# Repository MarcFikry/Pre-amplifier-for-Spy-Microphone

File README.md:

# Pre-amplifier for Spy Microphone 

## Project Overview
This project was carried out as part of the **1A Bureau d'Étude d'Électronique (Electronics Design Project)** at **Grenoble INP – Phelma**, during the first semester of the **Physics, Electronics and Telecommunications (PET)** engineering program.

The objective was to design and implement a **pre-amplifier for an electret microphone**, which could be later connected to an FM transmitter.  
Which includes the following functional blocks:
- Microphone biasing and pre-amplification
- Adjustable volume control
- Sound detection via a LED indicator

All circuits were powered under **asymmetrical supply (0–5 V)** and implemented using **MCP6002 operational amplifiers**.

---

## Features
- **Electret Microphone Biasing** — converts the small current variations from the microphone into voltage.  
- **Variable Gain Amplifier** — amplifies weak audio signals with adjustable sensitivity.  
- **Volume Control** — allows amplitude adjustment before the output stage to avoid distortion.  
- **Sound Detection LED** — implemented with a comparator with hysteresis to indicate when a sound is detected.  
- **Power Supply:** 0 – 5 V (single supply)  

---

## Design and Implementation
- Circuit **designed and simulated in KiCad**
- **Component sizing** based on theoretical transfer functions and Bode plots  
- **PCB routing** performed in KiCad, ensuring clean signal paths and proper grounding  
- **PCB manufacturing** followed by **manual soldering** and **experimental validation**  
- Tested using **oscilloscope** and **function generator** to verify:
  - Correct biasing
  - Amplification gain and frequency response
  - Proper LED threshold behavior

---

## Project Images

### Schematic Diagram  

### PCB Layout (Design in KiCad)  

### Printed PCB (Before Soldering)  

### Assembled Board (After Soldering)  

---

## Components Used
| Component | Description | Note |
|------------|--------------|------|
| MCP6002 | Dual Operational Amplifier | 0–5 V single-supply compatible |
| Electret Microphone | Audio input sensor | Requires biasing resistor |
| Resistors / Potentiometers | Gain and volume adjustment | E12 standard series |
| LED + Comparator | Sound level indicator | Implemented with hysteresis |
| Capacitors | AC coupling and filtering | 50 Hz–20 kHz bandpass design |

---

## Results
- Clean and stable amplification of the audio signal  
- Adjustable output amplitude via volume potentiometer  
- Reliable LED indication of detected sound  
- Measured gain and frequency response consistent with theoretical predictions  

---

## Tools and Environment
- **Software:** KiCad, Oscilloscope interface tools  
- **Hardware:** Breadboard, 0–5 V power supply, Function generator   

---

## Acknowledgments
Project supervised by:
- **Nicolas Ruty**
- **Fanny Poinsotte**
- **Matthieu Guerquin-Kern**

Grenoble INP – Phelma, 1A PET (Tronc Commun)

---

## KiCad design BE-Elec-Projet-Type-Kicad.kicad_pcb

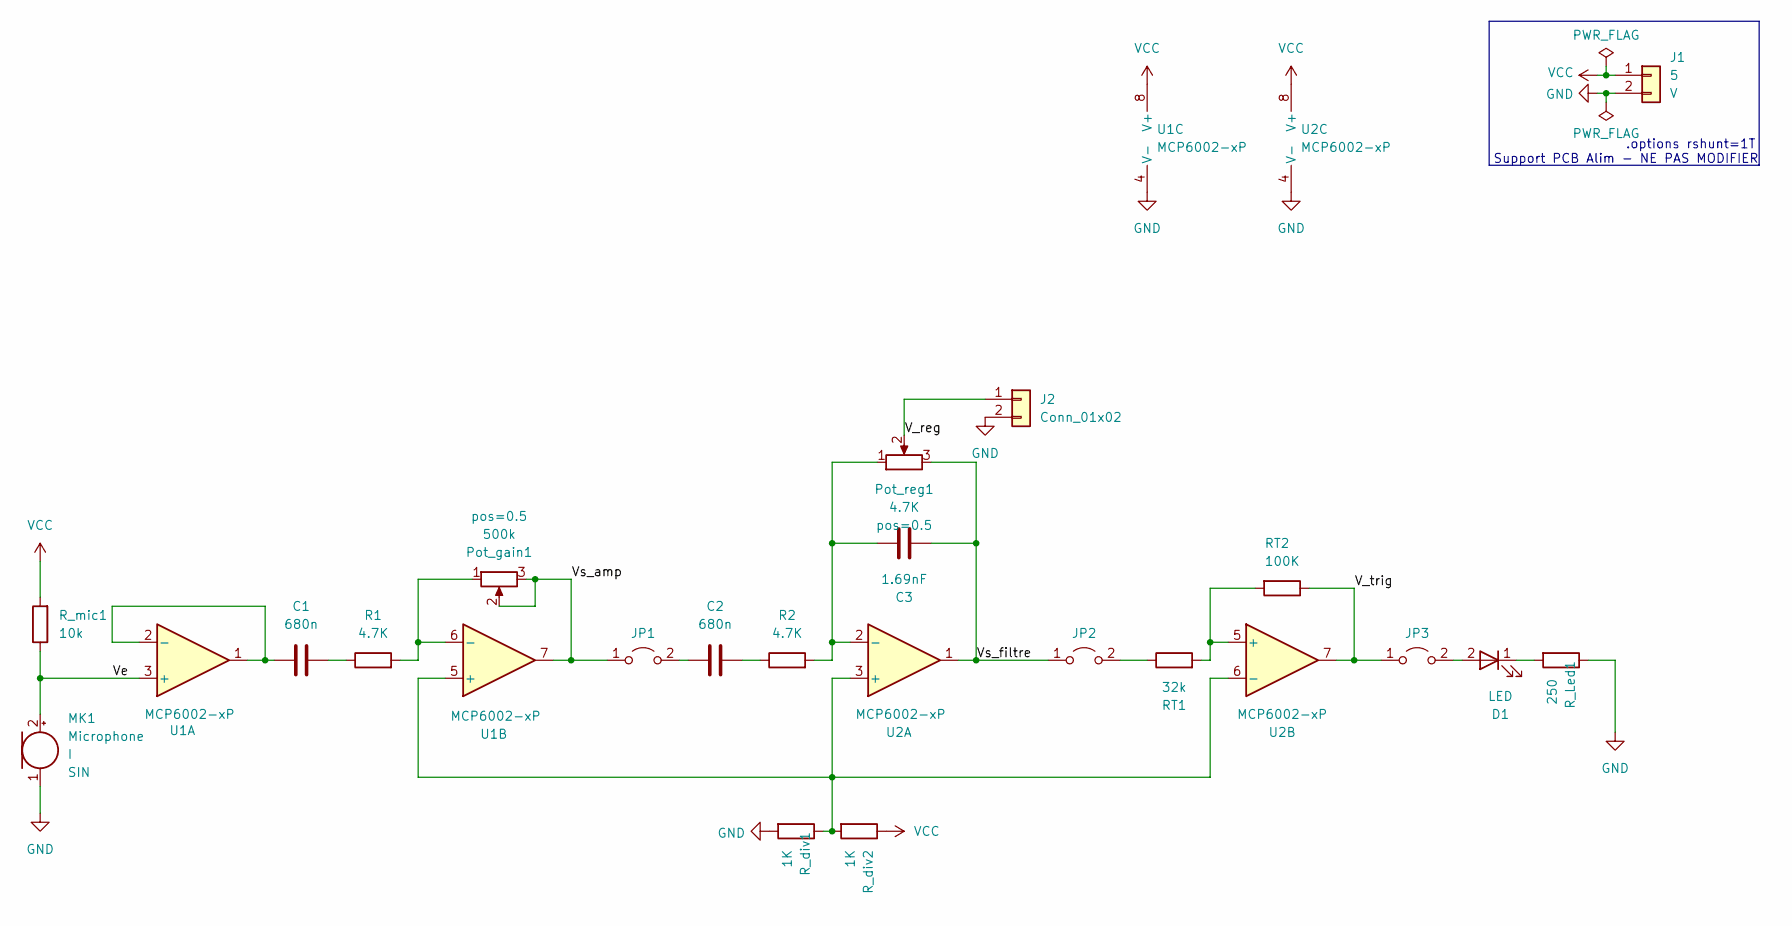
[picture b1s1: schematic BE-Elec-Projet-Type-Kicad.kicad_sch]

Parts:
C1, C2: 680n; CONDENSATEUR_5.08MM
C3: 1.69nF; CONDENSATEUR_5.08MM
D1: LED; LED_D5.0mm
J1: 5; PinHeader_1x02_P2.54mm_Vertical
J2: Conn_01x02; PinHeader_1x02_P2.54mm_Vertical
JP1, JP2, JP3: 1m; PinHeader_1x02_P2.54mm_Vertical
MK1: Microphone; PinHeader_1x02_P2.54mm_Vertical
Pot_gain1: 500k; Potentiometer_Piher_PT-10-V10_Vertical
Pot_reg1: 4.7K; Potentiometer_Piher_PT-10-V10_Vertical
R1, R2: 4.7K; R_Axial_DIN0207_L6.3mm_D2.5mm_P10.16mm_Horizontal
RT1: 32k; R_Axial_DIN0207_L6.3mm_D2.5mm_P10.16mm_Horizontal
RT2: 100K; R_Axial_DIN0207_L6.3mm_D2.5mm_P10.16mm_Horizontal
R_Led1: 250; R_Axial_DIN0207_L6.3mm_D2.5mm_P10.16mm_Horizontal
R_div1, R_div2: 1K; R_Axial_DIN0207_L6.3mm_D2.5mm_P10.16mm_Horizontal
R_mic1: 10k; R_Axial_DIN0207_L6.3mm_D2.5mm_P10.16mm_Horizontal
U1, U2: MCP6002-xP; DIP-8_W7.62mm_Socket_LongPads

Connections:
/V_reg: J2.1, Pot_reg1.2
/V_trig: JP3.1 (A), RT2.1, U2.7
/Ve: MK1.2 (+), R_mic1.1, U1.3 (+)
/Vs_amp: JP1.1 (A), Pot_gain1.2, Pot_gain1.3, U1.7
/Vs_filtre: C3.2, JP2.1 (A), Pot_reg1.3, U2.1
GND: J1.2, J2.2, MK1.1 (-), R_Led1.1, R_div1.2, U1.4 (V-), U2.4 (V-)
unnamed: C1.2, R1.1
unnamed: C2.2, R2.1
unnamed: D1.2 (A), JP3.2 (B)
unnamed: D1.1 (K), R_Led1.2
unnamed: C2.1, JP1.2 (B)
unnamed: JP2.2 (B), RT1.1
unnamed: C1.1, U1.1, U1.2 (-)
unnamed: R_div1.1, R_div2.2, U1.5 (+), U2.3 (+), U2.6 (-)
unnamed: Pot_gain1.1, R1.2, U1.6 (-)
unnamed: C3.1, Pot_reg1.1, R2.2, U2.2 (-)
unnamed: RT1.2, RT2.2, U2.5 (+)
VCC: J1.1, R_div2.1, R_mic1.2, U1.8 (V+), U2.8 (V+)

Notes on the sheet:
Support PCB Alim - NE PAS MODIFIER
.options rshunt=1T

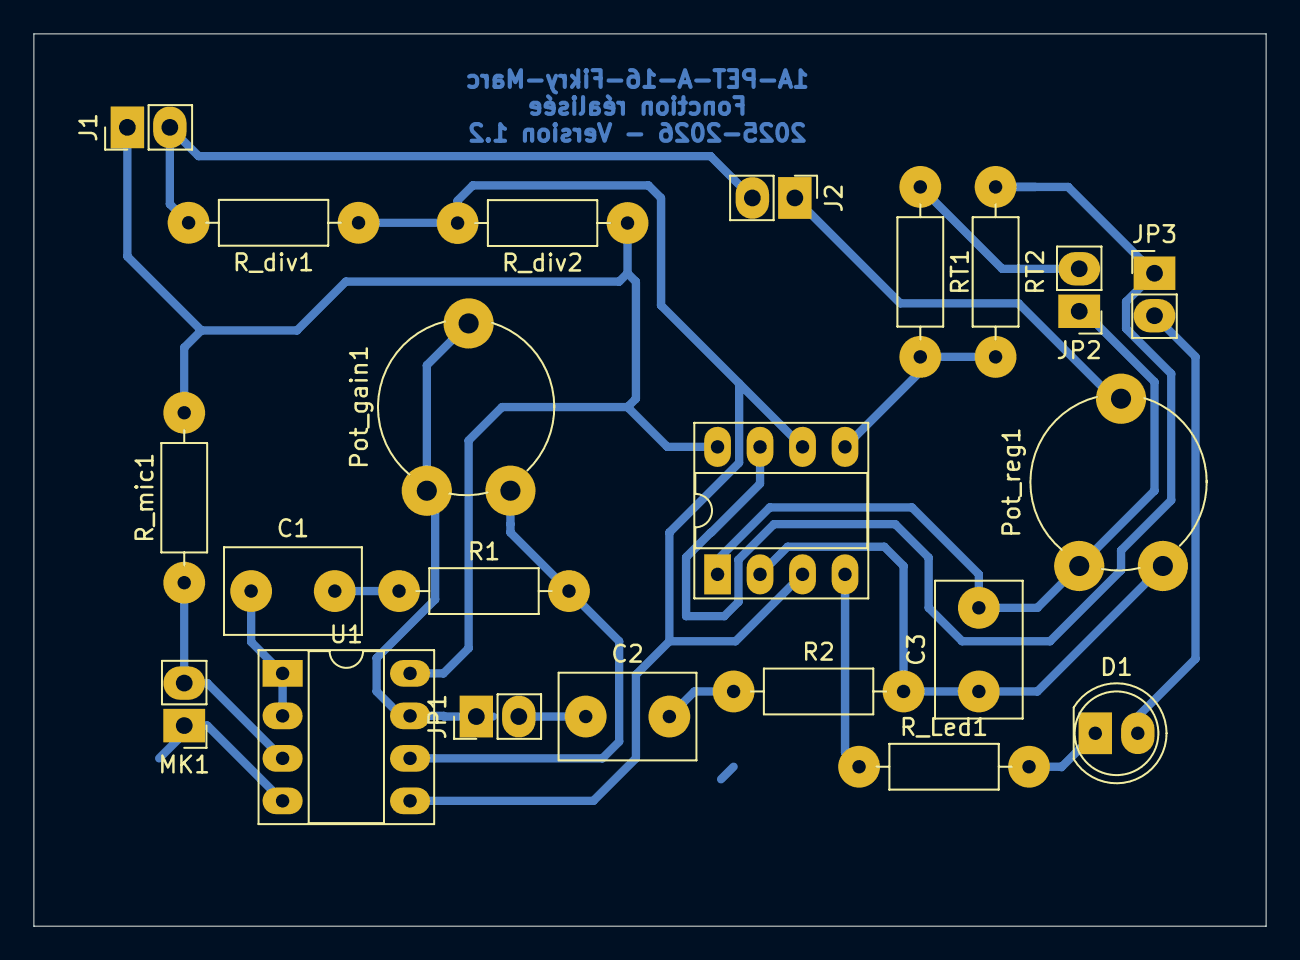
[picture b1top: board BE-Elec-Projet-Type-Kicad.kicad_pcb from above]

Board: 2 copper layers, 73.7 x 53.3 mm, 22 parts (0 on the bottom side), 18 nets.
